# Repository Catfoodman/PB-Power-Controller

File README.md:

# PB-Power-Controller
Power and Heat Bed controller for Printerbot Plus and similar units controlled by external ATX PSUs

## Folders:
	* PCB:
		* Contains PCB data - Eagle Schematics and Board files.
	 * Case:
	 	* Contains 3D Print files for case.
	
At this time this work is (C) Bruce Shipman and no license is granted for use

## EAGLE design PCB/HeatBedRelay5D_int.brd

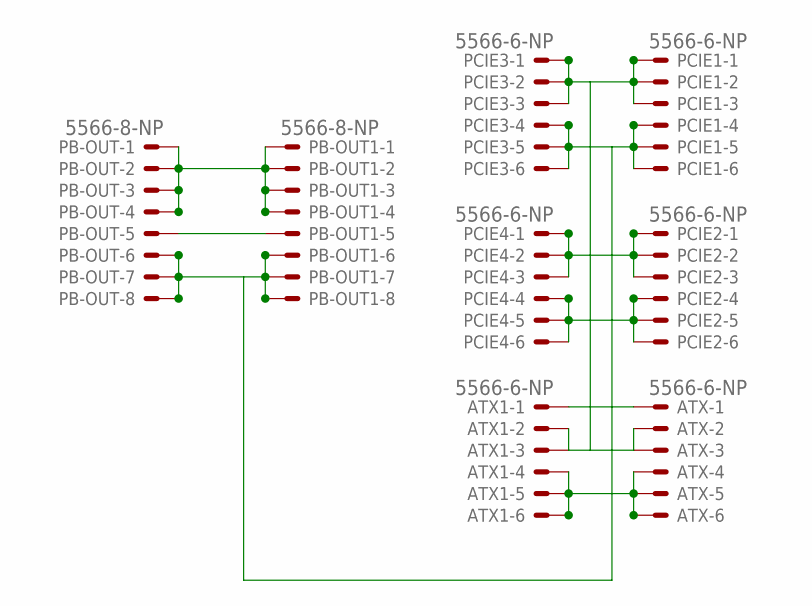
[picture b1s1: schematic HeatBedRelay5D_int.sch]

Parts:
ATX, ATX1: 5566-6-NP
PB-OUT, PB-OUT1: 5566-8-NP
PCIE1, PCIE2, PCIE3, PCIE4: 5566-6-NP

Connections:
12V: ATX.2, ATX.3, ATX1.2, ATX1.3, PCIE1.1, PCIE1.2, PCIE1.3, PCIE2.1, PCIE2.2, PCIE2.3, PCIE3.1, PCIE3.2, PCIE3.3, PCIE4.1, PCIE4.2, PCIE4.3
ATX_PWR_SW: ATX.1, ATX1.1
GND: ATX.4, ATX.5, ATX.6, ATX1.4, ATX1.5, ATX1.6, PB-OUT.6, PB-OUT.7, PB-OUT.8, PB-OUT1.6, PB-OUT1.7, PB-OUT1.8, PCIE1.4, PCIE1.5, PCIE1.6, PCIE2.4, PCIE2.5, PCIE2.6, PCIE3.4, PCIE3.5, PCIE3.6, PCIE4.4, PCIE4.5, PCIE4.6
PB_HB_ON: PB-OUT.5, PB-OUT1.5
PB_PWR: PB-OUT.1, PB-OUT.2, PB-OUT.3, PB-OUT.4, PB-OUT1.1, PB-OUT1.2, PB-OUT1.3, PB-OUT1.4

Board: 2 copper layers, 8 parts (0 on the bottom side), 5 nets, no tracks yet.

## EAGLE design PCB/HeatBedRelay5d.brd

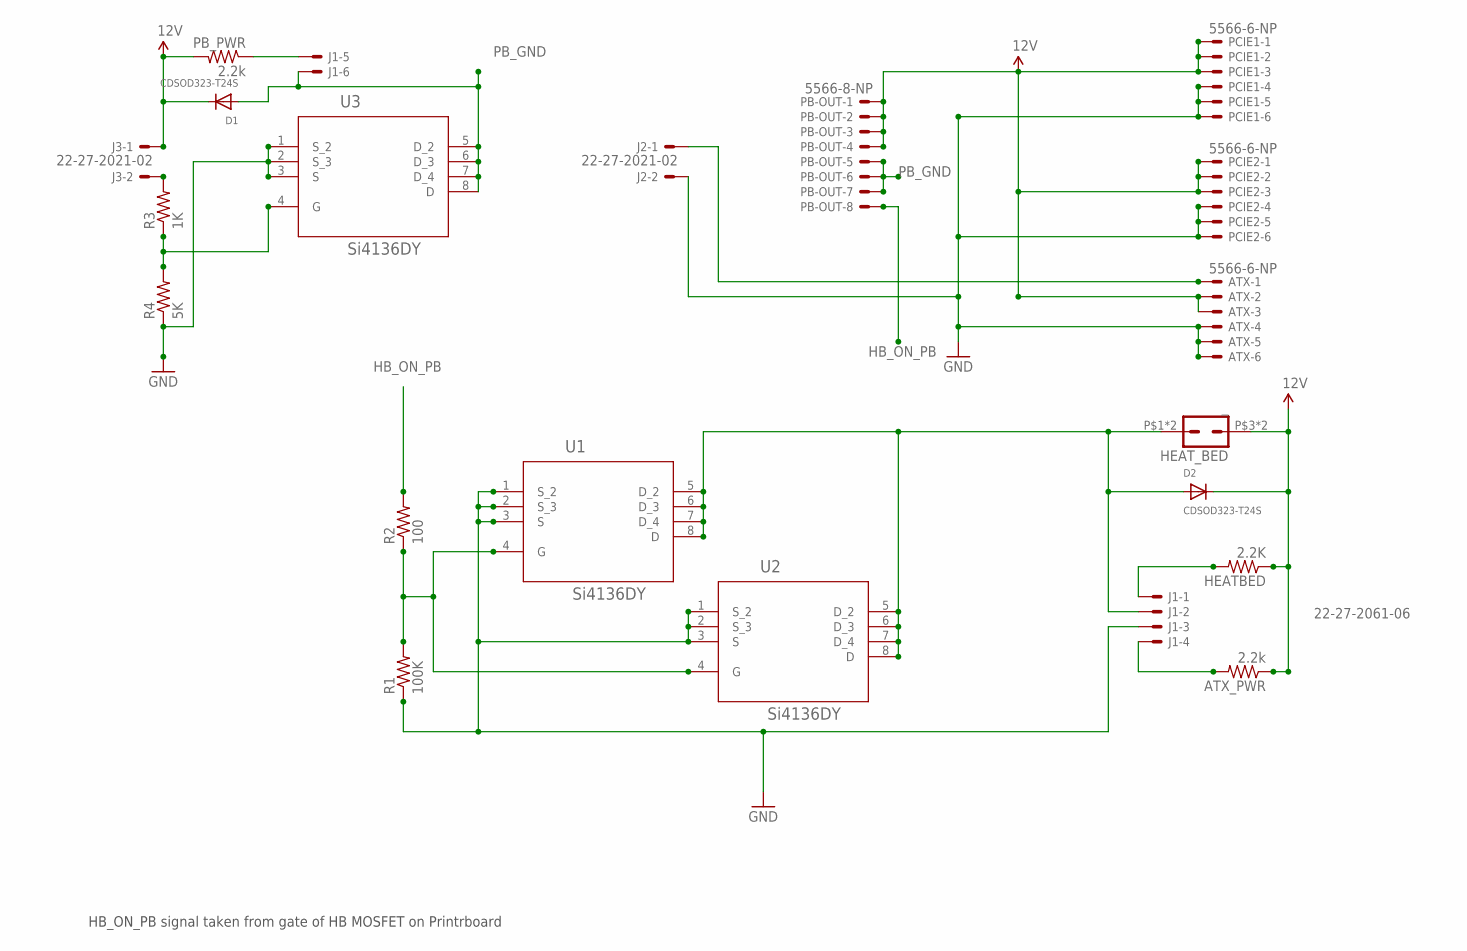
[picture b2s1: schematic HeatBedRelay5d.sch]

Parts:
ATX: 5566-6-NP
ATX_PWR: 2.2k; M1206
D1, D2: CDSOD323-T24S; SOD-323F
HEATBED: 2.2K; M1206
HEAT_BED: _; MOLEX_42820-2212
J1: 22-27-2061-06; 6410-06
J2, J3: 22-27-2021-02; 6410-02
PB-OUT: 5566-8-NP
PB_PWR: 2.2k; M1206
PCIE1, PCIE2: 5566-6-NP
R1: 100K; M1206
R2: 100; M1206
R3: 1K; M1206
R4: 5K; M1206
U1, U2, U3: Si4136DY; SOIC127P600X175-8N

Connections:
12V: ATX.2, ATX.3, ATX_PWR.1, D1.C, D2.C, HEATBED.1, HEAT_BED.P$3 (1), HEAT_BED.P$4 (1), J3.1, PB-OUT.1, PB-OUT.2, PB-OUT.3, PB-OUT.4, PB_PWR.2, PCIE1.1, PCIE1.2, PCIE1.3, PCIE2.1, PCIE2.2, PCIE2.3
GND: ATX.4, ATX.5, ATX.6, J1.3, J2.2, PCIE1.4, PCIE1.5, PCIE1.6, PCIE2.4, PCIE2.5, PCIE2.6, R1.1, R4.1, U1.1 (S_2), U1.2 (S_3), U1.3 (S), U2.1 (S_2), U2.2 (S_3), U2.3 (S), U3.1 (S_2), U3.2 (S_3), U3.3 (S)
HB_DRAIN: D2.A, HEAT_BED.P$1 (2), HEAT_BED.P$2 (2), J1.2, U1.5 (D_2), U1.6 (D_3), U1.7 (D_4), U1.8 (D), U2.5 (D_2), U2.6 (D_3), U2.7 (D_4), U2.8 (D)
HB_ON_PB: PB-OUT.8, R2.2
unnamed: ATX.1, J2.1
unnamed: HEATBED.2, J1.1
unnamed: ATX_PWR.2, J1.4
unnamed: R1.2, R2.1, U1.4 (G), U2.4 (G)
unnamed: J3.2, R3.2
unnamed: R3.1, R4.2, U3.4 (G)
unnamed: J1.5, PB_PWR.1
PB_GND: D1.A, J1.6, PB-OUT.5, PB-OUT.6, PB-OUT.7, U3.5 (D_2), U3.6 (D_3), U3.7 (D_4), U3.8 (D)

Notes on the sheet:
HB_ON_PB signal taken from gate of HB MOSFET on Printrboard

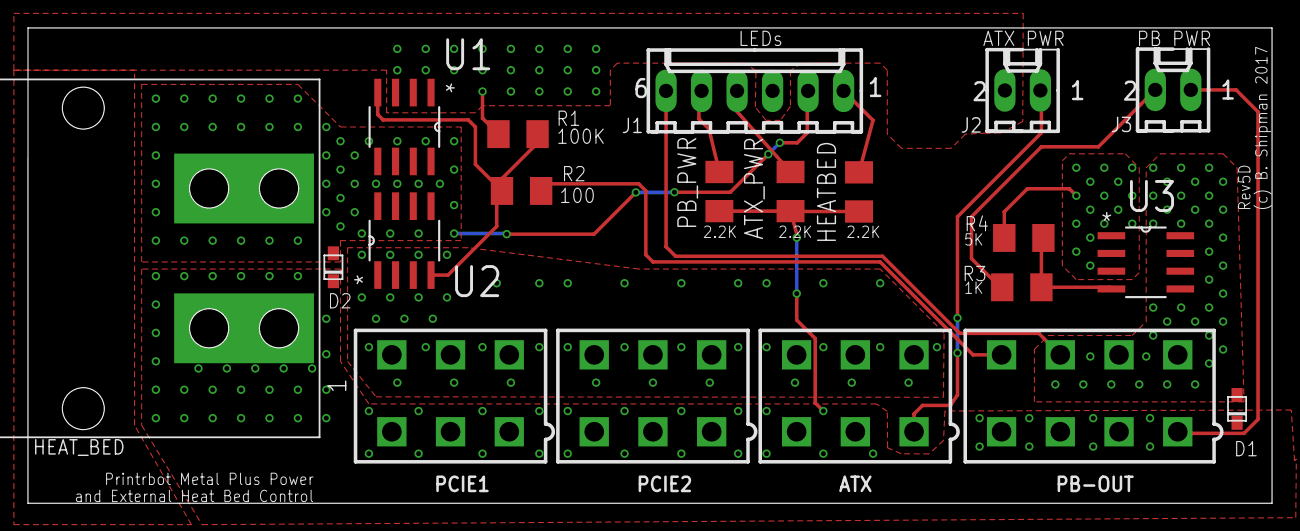
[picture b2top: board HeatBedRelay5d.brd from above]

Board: 2 copper layers, 89.0 x 34.0 mm, 20 parts (0 on the bottom side), 12 nets.
